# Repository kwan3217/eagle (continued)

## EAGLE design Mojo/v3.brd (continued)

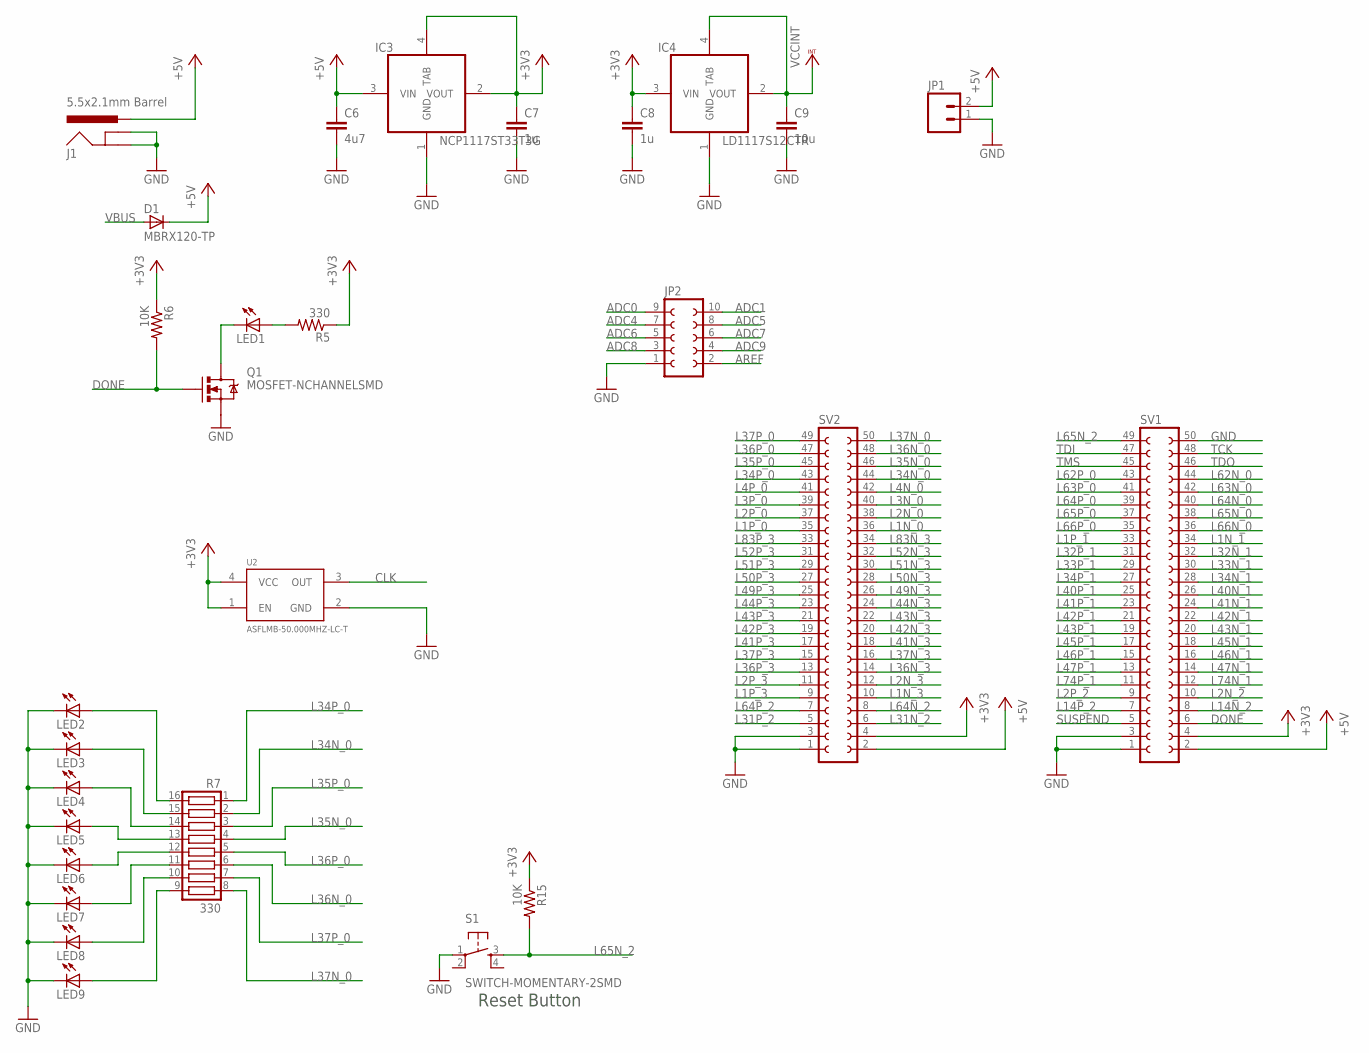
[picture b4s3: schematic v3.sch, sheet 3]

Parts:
C6: 4u7; C1206
C7, C8: 1u; C0603K
C9: 10u; C0603K
D1: MBRX120-TP; SOD123
IC3: NCP1117ST33T3G; SOT223
IC4: LD1117S12CTR; SOT223
J1: 5.5x2.1mm Barrel; POWER_JACK_SMD
JP1: M02PTH; 1X02
JP2: FE05-2
LED1, LED2, LED3, LED4, LED5, LED6, LED7, LED8, LED9: LED1206; LED-1206
Q1: MOSFET-NCHANNELSMD; SOT23-3
R5: 330; R0603
R6, R15: 10K; R0603
R7: 330; CTS743C163
S1: SWITCH-MOMENTARY-2SMD; TACTILE_SWITCH_SMD
SV1, SV2: FE25-2
U2: ASFLMB-50.000MHZ-LC-T; CRYSTAL-OSC-SMD-5X3

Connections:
+3V3: C7.1, C8.1, IC3.2 (VOUT), IC3.4 (TAB), IC4.3 (VIN), R5.1, R6.1, R15.1, SV1.4, SV2.4, U2.1 (EN), U2.4 (VCC); also elsewhere on the board
+5V: C6.1, D1.1 (C), IC3.3 (VIN), J1.VIN0 (PWR), JP1.2, SV1.2, SV2.2
ADC0: JP2.9; also elsewhere on the board
ADC1: JP2.10; also elsewhere on the board
ADC4: JP2.7; also elsewhere on the board
ADC5: JP2.8; also elsewhere on the board
ADC6: JP2.5; also elsewhere on the board
ADC7: JP2.6; also elsewhere on the board
ADC8: JP2.3; also elsewhere on the board
ADC9: JP2.4; also elsewhere on the board
AREF: JP2.2; also elsewhere on the board
CLK: U2.3 (OUT); also elsewhere on the board
DONE: Q1.1 (G), R6.2, SV1.6; also elsewhere on the board
GND: C6.2, C7.2, C8.2, C9.2, IC3.1 (GND), IC4.1 (GND), J1.GND (GNDBREAK), J1.P$4 (GND), JP1.1, JP2.1, LED2.C, LED3.C, LED4.C, LED5.C, LED6.C, LED7.C, LED8.C, LED9.C, Q1.2 (S), S1.1, SV1.1, SV1.3, SV1.50, SV2.1, SV2.3, U2.2 (GND); also elsewhere on the board
L1N_0: SV2.36; also elsewhere on the board
L1N_1: SV1.34; also elsewhere on the board
L1N_3: SV2.10; also elsewhere on the board
L1P_0: SV2.35; also elsewhere on the board
L1P_1: SV1.33; also elsewhere on the board
L1P_3: SV2.9; also elsewhere on the board
L2N_0: SV2.38; also elsewhere on the board
L2N_2: SV1.10; also elsewhere on the board
L2N_3: SV2.12; also elsewhere on the board
L2P_0: SV2.37; also elsewhere on the board
L2P_2: SV1.9; also elsewhere on the board
L2P_3: SV2.11; also elsewhere on the board
L3N_0: SV2.40; also elsewhere on the board
L3P_0: SV2.39; also elsewhere on the board
L4N_0: SV2.42; also elsewhere on the board
L4P_0: SV2.41; also elsewhere on the board
L14N_2: SV1.8; also elsewhere on the board
L14P_2: SV1.7; also elsewhere on the board
L31N_2: SV2.6; also elsewhere on the board
L31P_2: SV2.5; also elsewhere on the board
L32N_1: SV1.32; also elsewhere on the board
L32P_1: SV1.31; also elsewhere on the board
L33N_1: SV1.30; also elsewhere on the board
L33P_1: SV1.29; also elsewhere on the board
L34N_0: R7.2, SV2.44; also elsewhere on the board
L34N_1: SV1.28; also elsewhere on the board
L34P_0: R7.1, SV2.43; also elsewhere on the board
L34P_1: SV1.27; also elsewhere on the board
L35N_0: R7.4, SV2.46; also elsewhere on the board
L35P_0: R7.3, SV2.45; also elsewhere on the board
L36N_0: R7.6, SV2.48; also elsewhere on the board
L36N_3: SV2.14; also elsewhere on the board
L36P_0: R7.5, SV2.47; also elsewhere on the board
L36P_3: SV2.13; also elsewhere on the board
L37N_0: R7.8, SV2.50; also elsewhere on the board
L37N_3: SV2.16; also elsewhere on the board
L37P_0: R7.7, SV2.49; also elsewhere on the board
L37P_3: SV2.15; also elsewhere on the board
L40N_1: SV1.26; also elsewhere on the board
L40P_1: SV1.25; also elsewhere on the board
L41N_1: SV1.24; also elsewhere on the board
L41N_3: SV2.18; also elsewhere on the board
L41P_1: SV1.23; also elsewhere on the board
L41P_3: SV2.17; also elsewhere on the board
L42N_1: SV1.22; also elsewhere on the board
L42N_3: SV2.20; also elsewhere on the board
L42P_1: SV1.21; also elsewhere on the board
L42P_3: SV2.19; also elsewhere on the board
L43N_1: SV1.20; also elsewhere on the board
L43N_3: SV2.22; also elsewhere on the board
L43P_1: SV1.19; also elsewhere on the board
L43P_3: SV2.21; also elsewhere on the board
L44N_3: SV2.24; also elsewhere on the board
L44P_3: SV2.23; also elsewhere on the board
L45N_1: SV1.18; also elsewhere on the board
L45P_1: SV1.17; also elsewhere on the board
L46N_1: SV1.16; also elsewhere on the board
L46P_1: SV1.15; also elsewhere on the board
L47N_1: SV1.14; also elsewhere on the board
L47P_1: SV1.13; also elsewhere on the board
L49N_3: SV2.26; also elsewhere on the board
L49P_3: SV2.25; also elsewhere on the board
L50N_3: SV2.28; also elsewhere on the board
L50P_3: SV2.27; also elsewhere on the board
L51N_3: SV2.30; also elsewhere on the board
L51P_3: SV2.29; also elsewhere on the board
L52N_3: SV2.32; also elsewhere on the board
L52P_3: SV2.31; also elsewhere on the board
L62N_0: SV1.44; also elsewhere on the board
L62P_0: SV1.43; also elsewhere on the board
L63N_0: SV1.42; also elsewhere on the board
L63P_0: SV1.41; also elsewhere on the board
L64N_0: SV1.40; also elsewhere on the board
L64N_2: SV2.8; also elsewhere on the board
L64P_0: SV1.39; also elsewhere on the board
L64P_2: SV2.7; also elsewhere on the board
L65N_0: SV1.38; also elsewhere on the board
L65N_2: R15.2, S1.3, SV1.49; also elsewhere on the board
L65P_0: SV1.37; also elsewhere on the board
L66N_0: SV1.36; also elsewhere on the board
L66P_0: SV1.35; also elsewhere on the board
L74N_1: SV1.12; also elsewhere on the board
L74P_1: SV1.11; also elsewhere on the board
L83N_3: SV2.34; also elsewhere on the board
L83P_3: SV2.33; also elsewhere on the board
unnamed: LED1.A, R5.2
unnamed: LED1.C, Q1.3 (D)
unnamed: LED2.A, R7.16
unnamed: LED3.A, R7.15
unnamed: LED4.A, R7.14
unnamed: LED5.A, R7.13
unnamed: LED6.A, R7.12
unnamed: LED7.A, R7.11
unnamed: LED8.A, R7.10
unnamed: LED9.A, R7.9
SUSPEND: SV1.5; also elsewhere on the board
TCK: SV1.48; also elsewhere on the board
TDI: SV1.47; also elsewhere on the board
TDO: SV1.46; also elsewhere on the board
TMS: SV1.45; also elsewhere on the board
VBUS: D1.2 (A); also elsewhere on the board
VCCINT: C9.1, IC4.2 (VOUT), IC4.4 (TAB); also elsewhere on the board

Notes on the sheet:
Reset Button

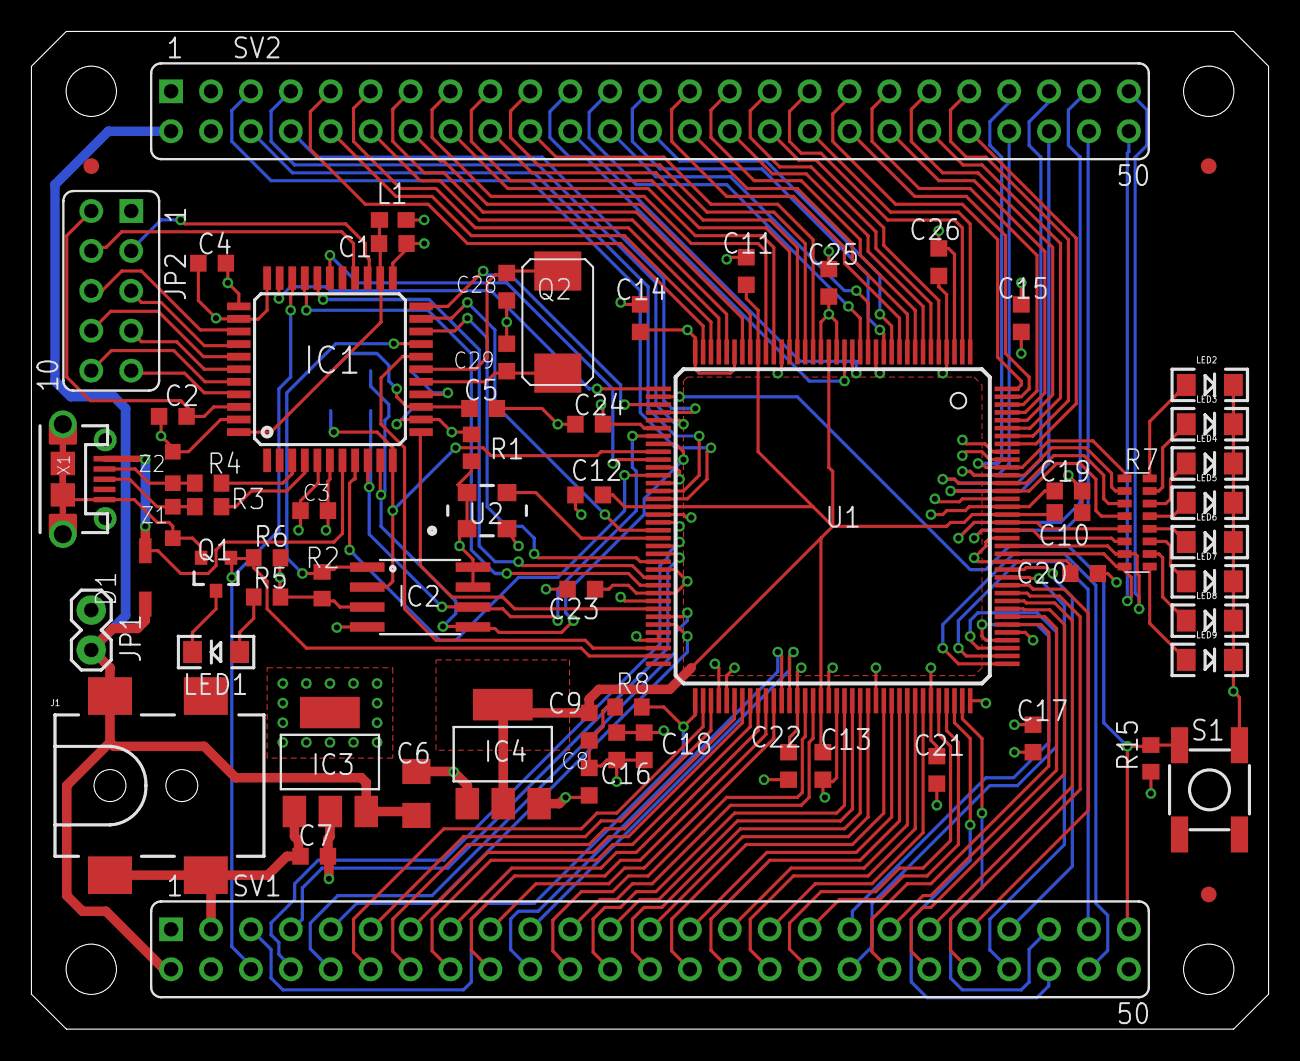
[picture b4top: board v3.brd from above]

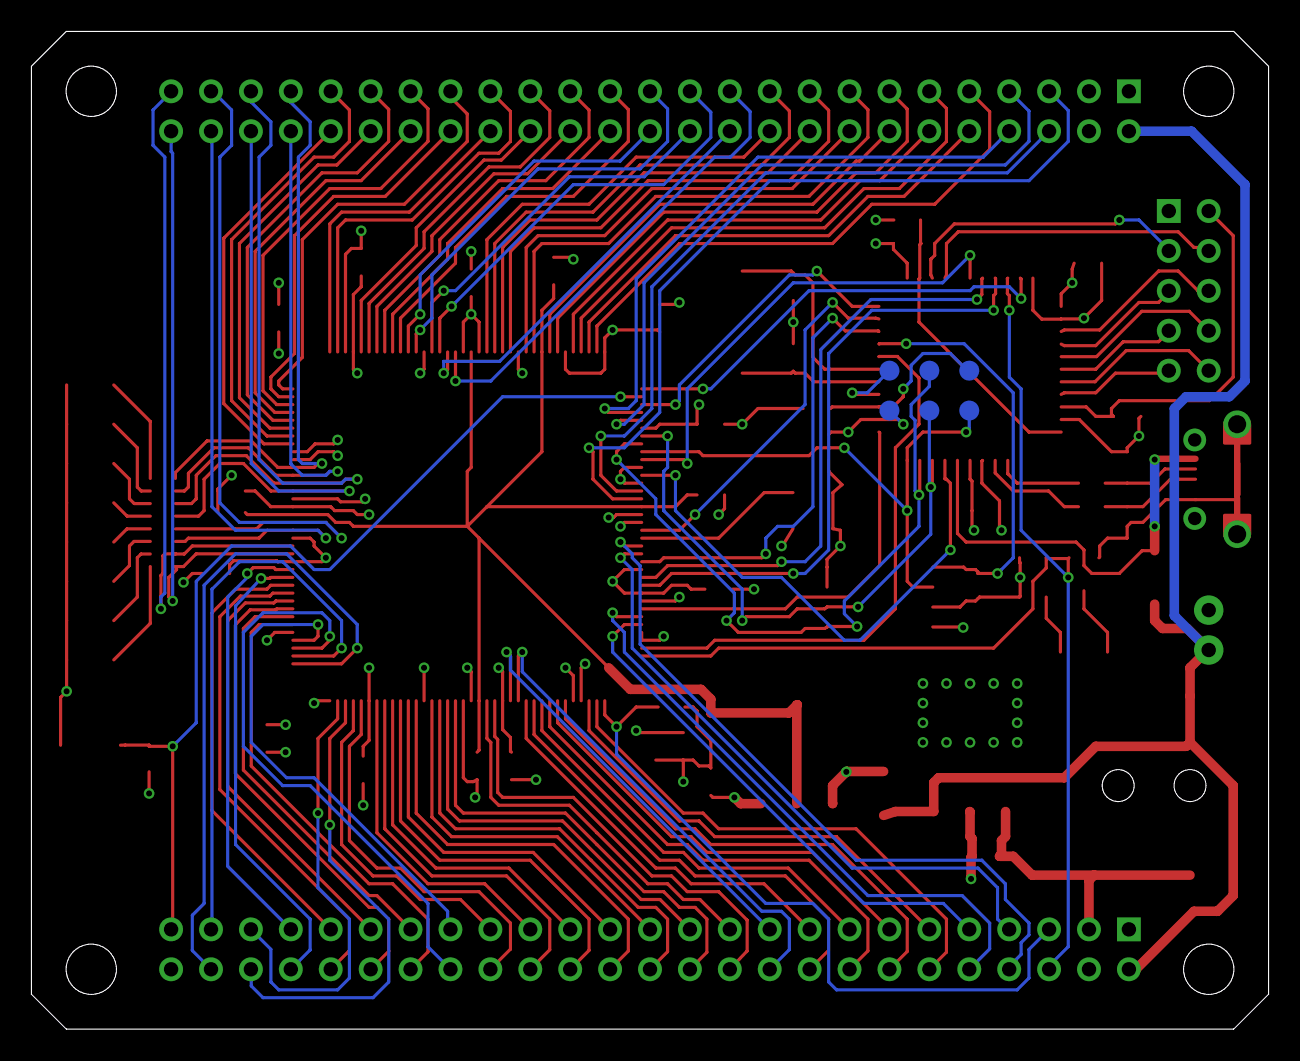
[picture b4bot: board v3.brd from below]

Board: 4 copper layers, 78.7 x 63.5 mm, 76 parts (7 on the bottom side), 138 nets.

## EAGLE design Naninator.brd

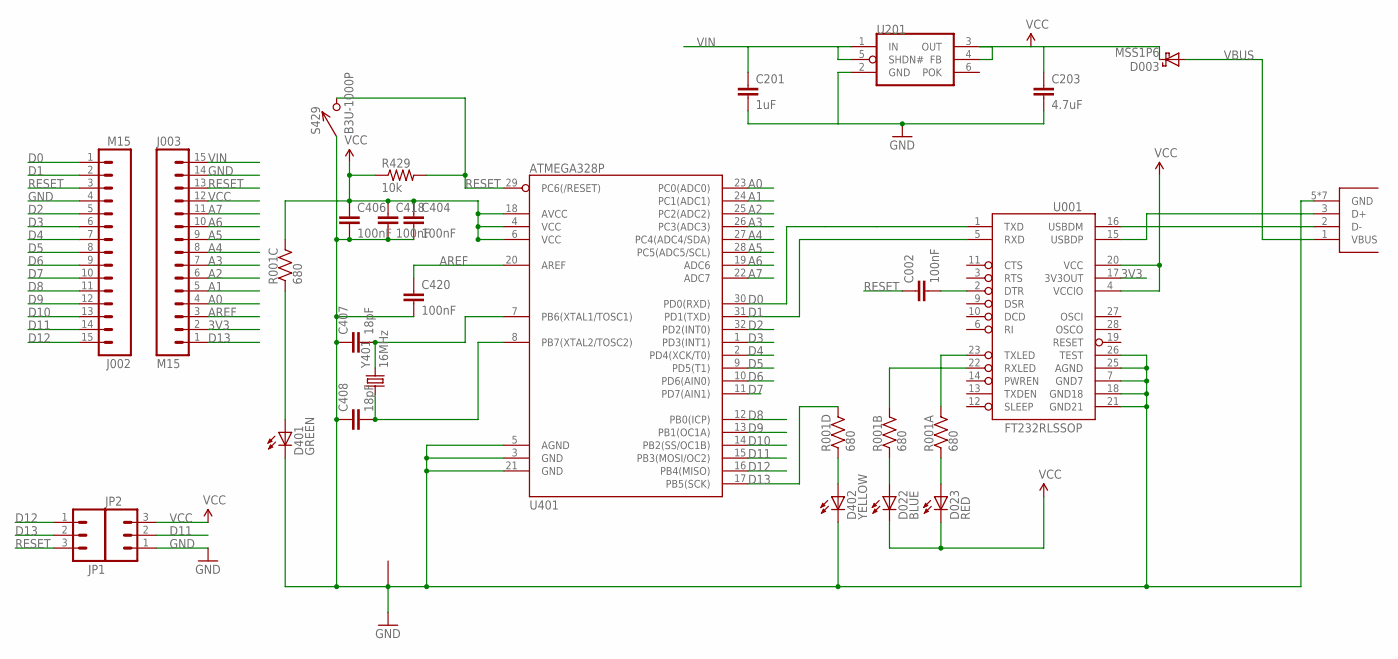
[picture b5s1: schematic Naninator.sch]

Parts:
C002, C404, C406, C418, C420: 100nF; 0402-CAP; DIGIKEY 445-1268-1-ND
C201: 1uF; 0402-CAP; DIGIKEY 445-1415-1-ND
C203: 4.7uF; 0402-CAP; DIGIKEY 445-7395-1-ND
C407, C408: 18pF; 0402-CAP; DIGIKEY 445-1238-1-ND
D003: MSS1P6; MICROSMP; DIGIKEY MSS1P6-M3/89AGICT-ND
D022: BLUE; LED-0603; DIGIKEY 350-2037-1-ND
D023: RED; LED-0603; DIGIKEY 754-1359-1-ND
D401: GREEN; LED-0603; DIGIKEY 350-2036-1-ND
D402: YELLOW; LED-0603; DIGIKEY 754-1124-1-ND
J001: USB_MICROB_JST; UB-MC5BR3-SD204-4S; DIGIKEY 455-2562-1-ND
J002, J003: M15; 1X15; DIGIKEY $NOPART
JP1, JP2: M03PTH; 1X03; DIGIKEY $NOPART
R001: 680; CRA04; DIGIKEY CRA4S8680CT-ND
R429: 10k; 0402-RES; DIGIKEY P10.0KLCT-ND
S429: B3U-1000P
U001: FT232RLSSOP; SSOP28DB; DIGIKEY 768-1007-1-ND
U201: MAX8881; SOT-23-6; DIGIKEY MAX8881EUT50+TCT-ND
U401: ATMEGA328P; TQFP32-08; DIGIKEY ATMEGA328P-15AZCT-ND
Y401: 16MHz; CRYSTAL_SMD_2MM_2_5MM; DIGIKEY 478-6955-1-ND

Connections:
3V3: J003.2, U001.17 (3V3OUT)
A0: J003.4, U401.23 (PC0(ADC0))
A1: J003.5, U401.24 (PC1(ADC1))
A2: J003.6, U401.25 (PC2(ADC2))
A3: J003.7, U401.26 (PC3(ADC3))
A4: J003.8, U401.27 (PC4(ADC4/SDA))
A5: J003.9, U401.28 (PC5(ADC5/SCL))
A6: J003.10, U401.19 (ADC6)
A7: J003.11, U401.22 (ADC7)
AREF: C420.1, J003.3, U401.20 (AREF)
D0: J002.1, U001.1 (TXD), U401.30 (PD0(RXD))
D1: J002.2, U001.5 (RXD), U401.31 (PD1(TXD))
D2: J002.5, U401.32 (PD2(INT0))
D3: J002.6, U401.1 (PD3(INT1))
D4: J002.7, U401.2 (PD4(XCK/T0))
D5: J002.8, U401.9 (PD5(T1))
D6: J002.9, U401.10 (PD6(AIN0))
D7: J002.10, U401.11 (PD7(AIN1))
D8: J002.11, U401.12 (PB0(ICP))
D9: J002.12, U401.13 (PB1(OC1A))
D10: J002.13, U401.14 (PB2(SS/OC1B))
D11: J002.14, JP2.2, U401.15 (PB3(MOSI/OC2))
D12: J002.15, JP1.1, U401.16 (PB4(MISO))
D13: J003.1, JP1.2, R001.5 (2), U401.17 (PB5(SCK))
DTR#: C002.2, U001.2 (DTR)
GND: C201.2, C203.2, C404.2, C406.2, C407.1, C408.1, C418.2, C420.2, D401.C, D402.C, J001.5 (GND), J001.P$6 (GND), J001.P$7 (GND), J001.P$8 (GND), J001.P$9 (GND), J001.P$10 (GND), J001.P$11 (GND), J002.4, J003.14, JP2.1, S429.P$1 (1), U001.7 (GND7), U001.18 (GND18), U001.21 (GND21), U001.25 (AGND), U001.26 (TEST), U201.2 (GND), U401.3 (GND), U401.5 (AGND), U401.21 (GND), Y401.2 (1), Y401.4 (1)
unnamed: C407.2, U401.7 (PB6(XTAL1/TOSC1)), Y401.3 (2)
unnamed: C408.2, U401.8 (PB7(XTAL2/TOSC2)), Y401.1
unnamed: J001.3 (D+), U001.15 (USBDP)
unnamed: J001.2 (D-), U001.16 (USBDM)
unnamed: D401.A, R001.3 (1)
unnamed: D402.A, R001.4 (1)
unnamed: D023.A, R001.1
unnamed: D022.A, R001.2 (1)
RESET: C002.1, J002.3, J003.13, JP1.3, R429.2, S429.P$2 (2), U401.29 (PC6(/RESET))
RXLED1: R001.7 (2), U001.22 (RXLED)
TXLED1: R001.8 (2), U001.23 (TXLED)
VBUS: D003.A, J001.1 (VBUS)
VCC: C203.1, C404.1, C406.1, C418.1, D003.K, D022.C, D023.C, J003.12, JP2.3, R001.6 (2), R429.1, U001.4 (VCCIO), U001.20 (VCC), U201.3 (OUT), U201.4 (FB), U401.4 (VCC), U401.6 (VCC), U401.18 (AVCC)
VIN: C201.1, J003.15, U201.1 (IN), U201.5 (SHDN#)

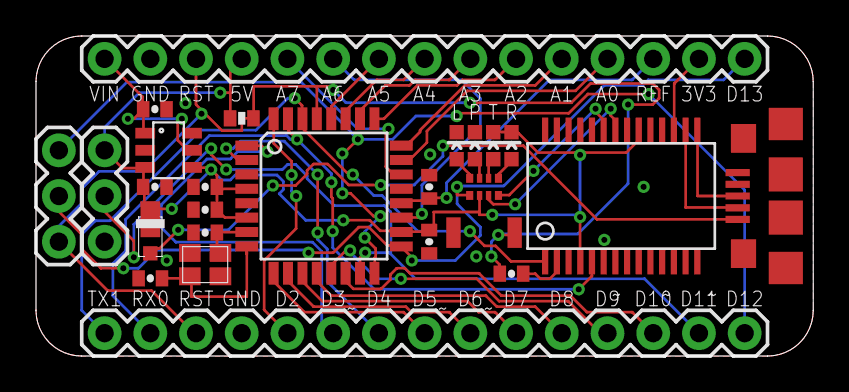
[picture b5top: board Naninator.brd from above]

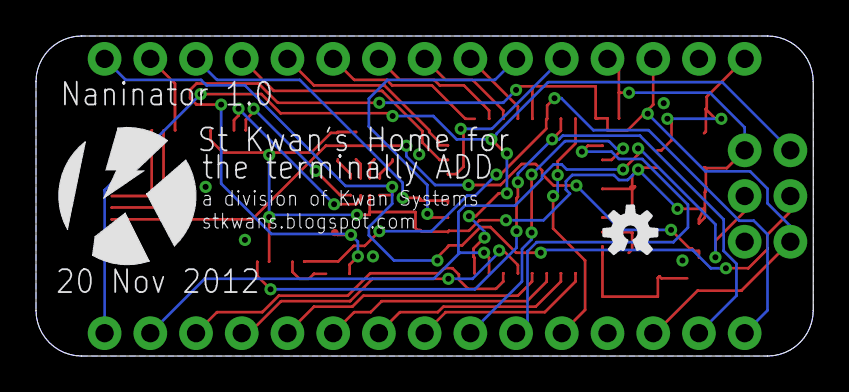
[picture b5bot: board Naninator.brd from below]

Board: 2 copper layers, 43.2 x 17.8 mm, 28 parts (2 on the bottom side), 40 nets.

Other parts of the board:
U$1: KWAN_CIRCLE
U$2: OSHW-LOGO-S

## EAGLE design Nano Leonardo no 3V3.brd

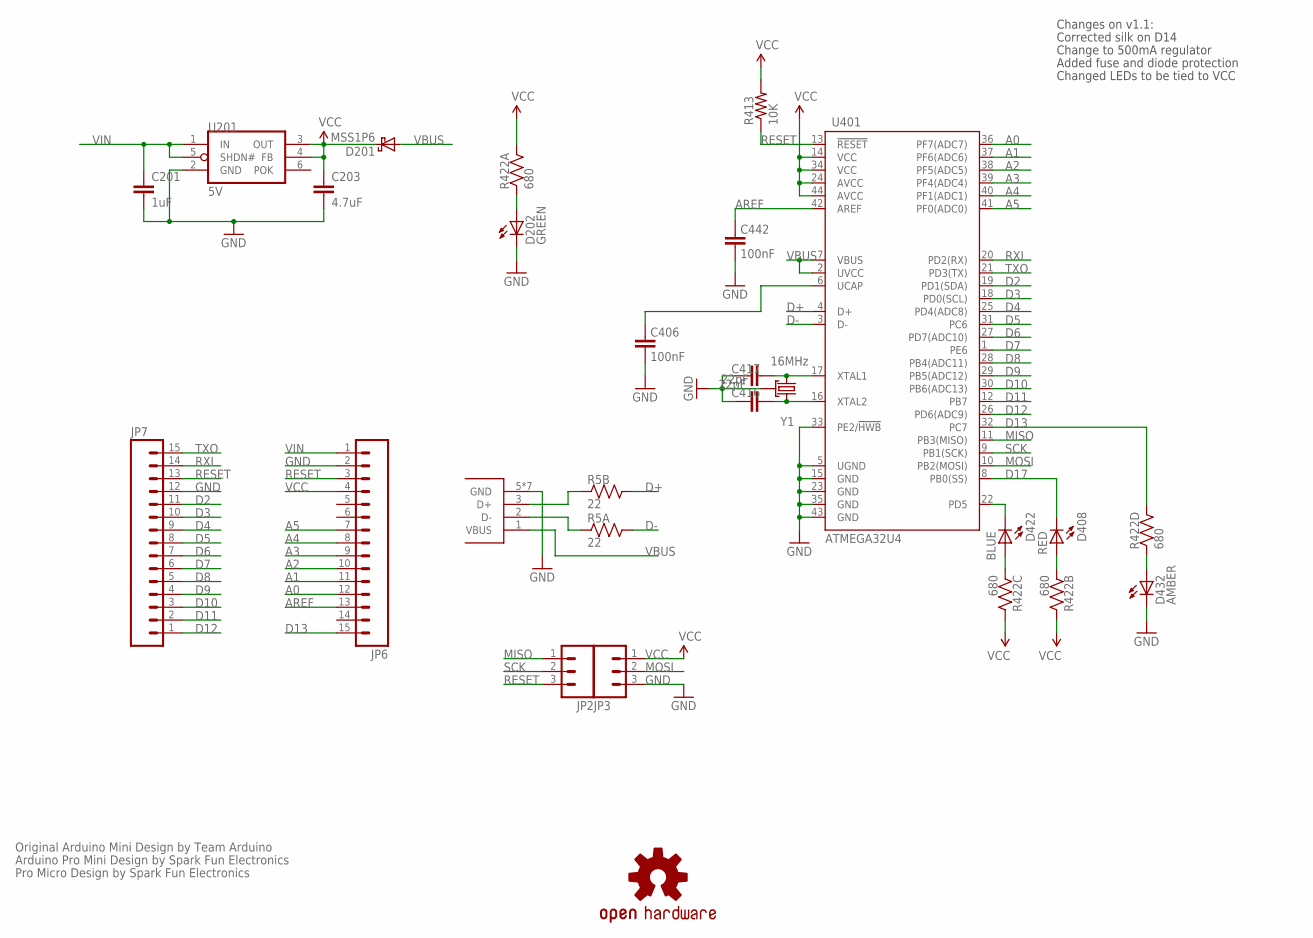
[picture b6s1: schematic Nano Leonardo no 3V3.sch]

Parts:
C201: 1uF; 0402-CAP; DIGIKEY 445-1415-1-ND
C203: 4.7uF; 0402-CAP; DIGIKEY 445-7395-1-ND
C406, C442: 100nF; 0402-CAP
C416, C417: 22pF; 0402-CAP
D201: MSS1P6; MICROSMP; DIGIKEY MSS1P6-M3/89AGICT-ND
D202: GREEN; LED-0603
D408: RED; LED-0603
D422: BLUE; LED-0603
D432: AMBER; LED-0603
JP2, JP3: M031X03_NO_SILK; 1X03_NO_SILK
JP6, JP7: M15; 1X15
R5: 22; CRA02
R413: 10K; 0402-RES
R422: 680; CRA04
U201: 5V; SOT-23-6; DIGIKEY MAX8881EUT50+TCT-ND
U401: ATMEGA32U4; QFN-44-NOPAD
U$3: OSHW-LOGOS; OSHW-LOGO-S
X1: USB_MICROB_JSTGCT; USB_MICROB_3075
Y1: 16MHz; CRYSTAL_SMD_2MM_2_5MM

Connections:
A0: JP6.12, U401.36 (PF7(ADC7))
A1: JP6.11, U401.37 (PF6(ADC6))
A2: JP6.10, U401.38 (PF5(ADC5))
A3: JP6.9, U401.39 (PF4(ADC4))
A4: JP6.8, U401.40 (PF1(ADC1))
A5: JP6.7, U401.41 (PF0(ADC0))
AREF: C442.2, JP6.13, U401.42 (AREF)
D2: JP7.11, U401.19 (PD1(SDA))
D3: JP7.10, U401.18 (PD0(SCL))
D4: JP7.9, U401.25 (PD4(ADC8))
D5: JP7.8, U401.31 (PC6)
D6: JP7.7, U401.27 (PD7(ADC10))
D7: JP7.6, U401.1 (PE6)
D8: JP7.5, U401.28 (PB4(ADC11))
D9: JP7.4, U401.29 (PB5(ADC12))
D10: JP7.3, U401.30 (PB6(ADC13))
D11: JP7.2, U401.12 (PB7)
D12: JP7.1, U401.26 (PD6(ADC9))
D13: JP6.15, R422.5 (2), U401.32 (PC7)
D17: D408.C, U401.8 (PB0(SS))
D+: R5.3 (2), U401.4 (D+)
D-: R5.4 (2), U401.3 (D-)
GND: C201.2, C203.2, C406.1, C416.2, C417.2, C442.1, D202.C, D432.C, JP3.3, JP6.2, JP7.12, U201.2 (GND), U401.5 (UGND), U401.15 (GND), U401.23 (GND), U401.33 (PE2/!HWB), U401.35 (GND), U401.43 (GND), X1.5 (GND), X1.P$1 (GND), X1.P$2 (GND), X1.P$3 (GND), X1.P$4 (GND), X1.P$8 (GND), X1.P$10 (GND), Y1.2 (GND), Y1.4 (GND)
MISO: JP2.1, U401.11 (PB3(MISO))
MOSI: JP3.2, U401.10 (PB2(MOSI))
unnamed: D422.A, R422.3 (1)
unnamed: D408.A, R422.2 (1)
unnamed: D432.A, R422.4 (1)
unnamed: C406.2, U401.6 (UCAP)
unnamed: R5.1, X1.2 (D-)
unnamed: R5.2 (1), X1.3 (D+)
unnamed: D202.A, R422.1
RESET: JP2.3, JP6.3, JP7.13, R413.1, U401.13 (!RESET)
RXI: JP7.14, U401.20 (PD2(RX))
SCK: JP2.2, U401.9 (PB1(SCK))
TXLED: D422.C, U401.22 (PD5)
TXO: JP7.15, U401.21 (PD3(TX))
VBUS: D201.A, U401.2 (UVCC), U401.7 (VBUS), X1.1 (VBUS)
VCC: C203.1, D201.K, JP3.1, JP6.4, R413.2, R422.6 (2), R422.7 (2), R422.8 (2), U201.3 (OUT), U201.4 (FB), U401.14 (VCC), U401.24 (AVCC), U401.34 (VCC), U401.44 (AVCC)
VIN: C201.1, JP6.1, U201.1 (IN), U201.5 (SHDN#)
XTAL1: C417.1, U401.17 (XTAL1), Y1.1
XTAL2: C416.1, U401.16 (XTAL2), Y1.3 (2)

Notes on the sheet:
Original Arduino Mini Design by Team Arduino
Arduino Pro Mini Design by Spark Fun Electronics
Pro Micro Design by Spark Fun Electronics
Changes on v1.1:
Corrected silk on D14
Change to 500mA regulator
Added fuse and diode protection
Changed LEDs to be tied to VCC

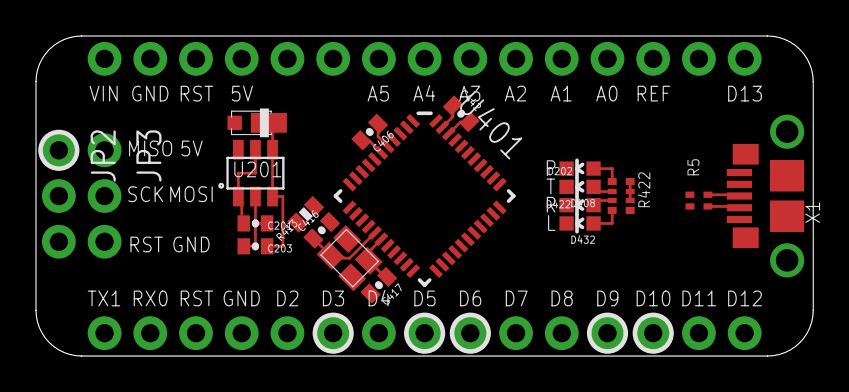
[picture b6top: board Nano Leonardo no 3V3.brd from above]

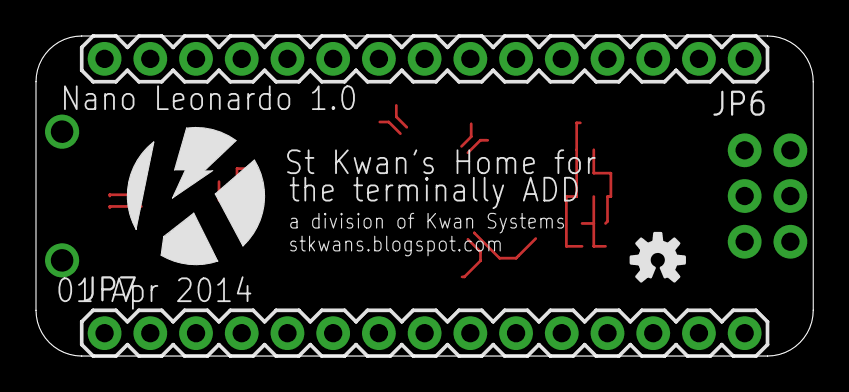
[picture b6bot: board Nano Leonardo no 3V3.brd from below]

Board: 2 copper layers, 43.2 x 17.8 mm, 24 parts (4 on the bottom side), 42 nets.

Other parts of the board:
U$1: KWAN_CIRCLE
